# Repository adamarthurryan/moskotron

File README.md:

moskotron
=========

A unique analog audio synthesizer. Built with and for Alex Moskos - aka Drainolith. 

Audio is generated by a Korg Monotron, which is extended by wiring in two new boards: 
an ADSR enveloped waveshaper and a 5-key tunable touch keyboard.
The keyboard can be tuned to any scale - conventional, microtonal or weird.

The entire synthesizer was encased in a book - for effect.

See http://madanworb.com/blog/2012/08/15/moskotron/ for video of Alex trying it out for the first time.

Schematics and burnable pcb layouts are available in the documentation folder.

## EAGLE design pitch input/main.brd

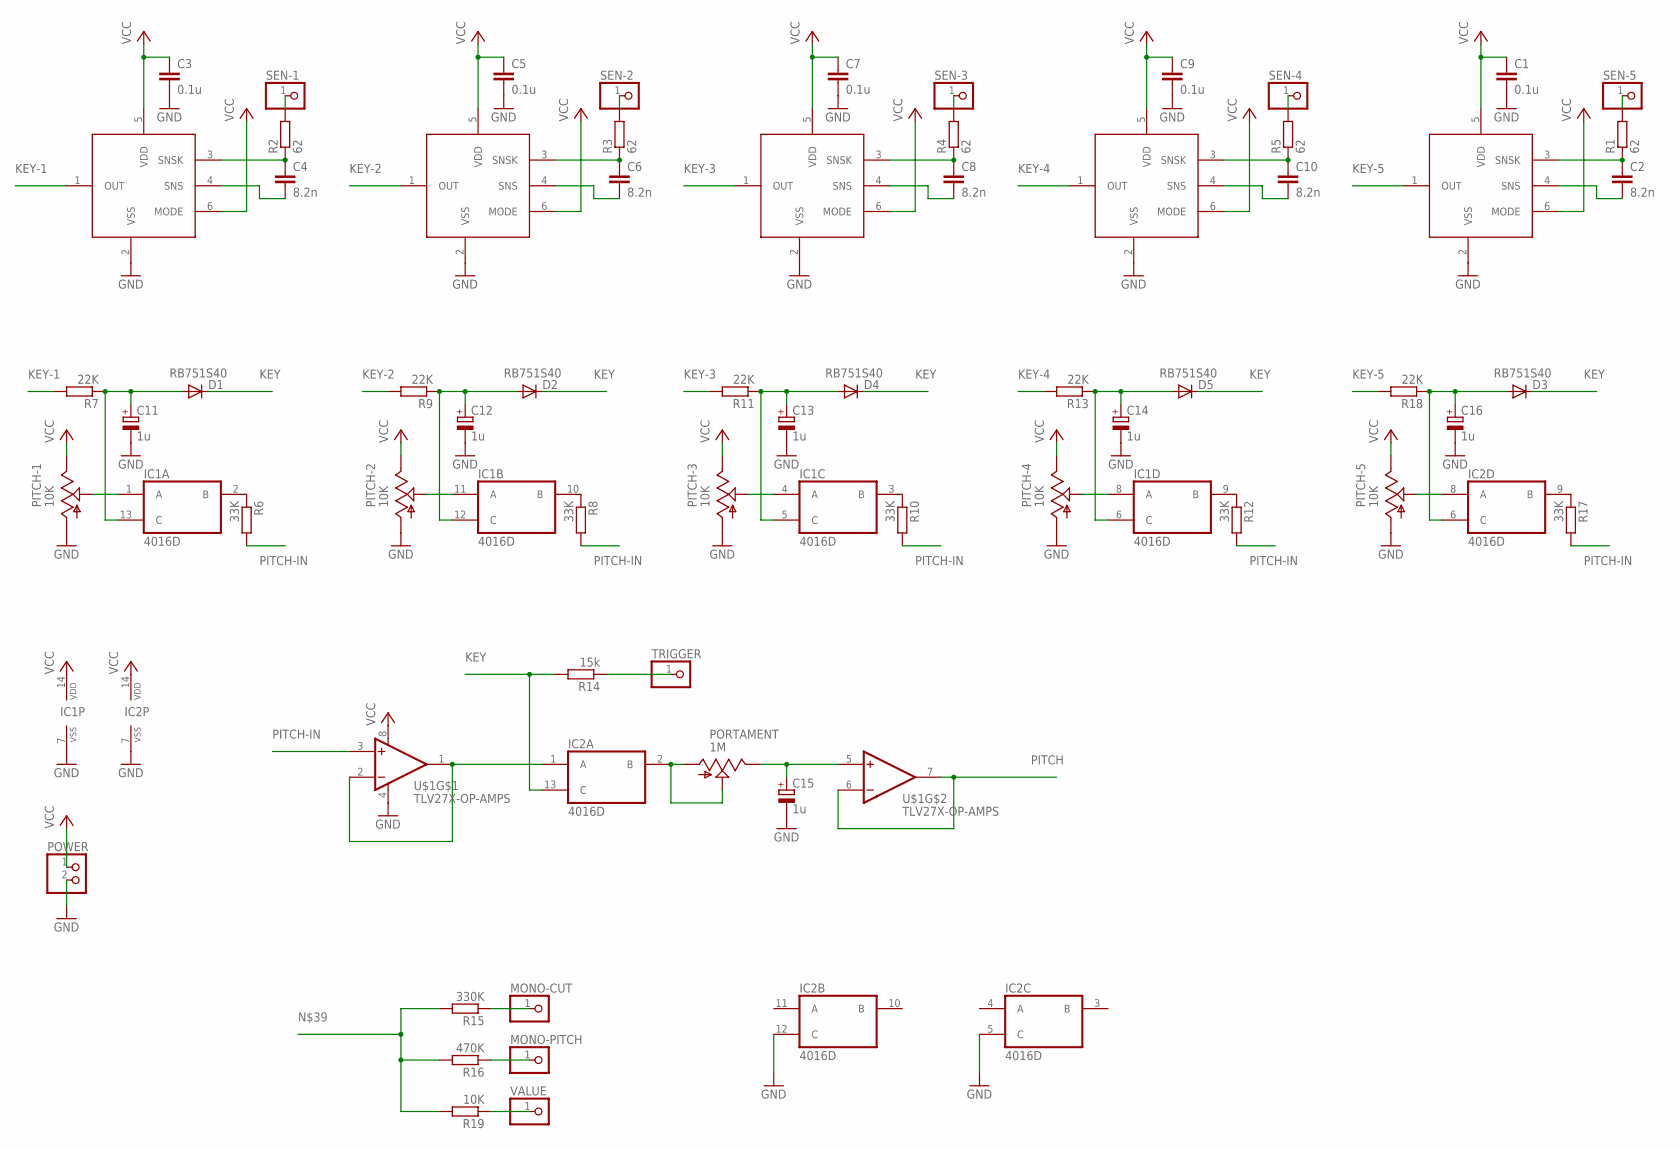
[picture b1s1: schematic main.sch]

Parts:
C1, C3, C5, C7, C9: 0.1u; C0805
C2, C4, C6, C8, C10: 8.2n; C0805
C11, C12, C13, C14, C15, C16: 1u; PANASONIC_A
D1, D2, D3, D4, D5: RB751S40; SOD523
IC1, IC2: 4016D; SO14
MONO-CUT: PINHD-1X1; 1X01
MONO-PITCH: PINHD-1X1; 1X01
PITCH-1, PITCH-2, PITCH-3, PITCH-4, PITCH-5: 10K; PIN-1X03
PORTAMENT: 1M; PIN-1X03
POWER: PINHD-1X2; 1X02
R1, R2, R3, R4, R5: 62; R0805
R6, R8, R10, R12, R17: 33K; R0805
R7, R9, R11, R13, R18: 22K; R0805
R14: 15k; R0805
R15: 330K; R0805
R16: 470K; R0805
R19: 10K; R0805
SEN-1, SEN-2, SEN-3, SEN-4, SEN-5: PINHD-1X1; 1X01
TRIGGER: PINHD-1X1; 1X01
U$1: TLV27X-OP-AMPS; SOIC8
U$2, U$3, U$4, U$5, U$6: AT42QT1010; SOT23-6L
VALUE: PINHD-1X1; 1X01

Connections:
GND: C1.2, C3.2, C5.2, C7.2, C9.2, C11.-, C12.-, C13.-, C14.-, C15.-, C16.-, IC1.7 (VSS), IC2.5 (C), IC2.7 (VSS), IC2.12 (C), PITCH-1.1 (A), PITCH-2.1 (A), PITCH-3.1 (A), PITCH-4.1 (A), PITCH-5.1 (A), POWER.2, U$1.4 (V-), U$2.2 (VSS), U$3.2 (VSS), U$4.2 (VSS), U$5.2 (VSS), U$6.2 (VSS)
KEY: D1.C, D2.C, D3.C, D4.C, D5.C, IC2.13 (C), R14.2
KEY-1: R7.2, U$2.1 (OUT)
KEY-2: R9.2, U$3.1 (OUT)
KEY-3: R11.2, U$4.1 (OUT)
KEY-4: R13.2, U$5.1 (OUT)
KEY-5: R18.2, U$6.1 (OUT)
unnamed: C4.2, U$2.4 (SNS)
unnamed: C4.1, R2.1, U$2.3 (SNSK)
unnamed: R2.2, SEN-1.1
unnamed: C6.2, U$3.4 (SNS)
unnamed: C6.1, R3.1, U$3.3 (SNSK)
unnamed: R3.2, SEN-2.1
unnamed: C8.2, U$4.4 (SNS)
unnamed: C8.1, R4.1, U$4.3 (SNSK)
unnamed: R4.2, SEN-3.1
unnamed: C10.2, U$5.4 (SNS)
unnamed: C10.1, R5.1, U$5.3 (SNSK)
unnamed: R5.2, SEN-4.1
unnamed: IC1.1 (A), PITCH-1.2 (S)
unnamed: IC1.2 (B), R6.1
unnamed: C11.+, D1.A, IC1.13 (C), R7.1
unnamed: IC1.11 (A), PITCH-2.2 (S)
unnamed: IC1.10 (B), R8.1
unnamed: C12.+, D2.A, IC1.12 (C), R9.1
unnamed: IC1.4 (A), PITCH-3.2 (S)
unnamed: IC1.3 (B), R10.1
unnamed: C13.+, D4.A, IC1.5 (C), R11.1
unnamed: IC1.8 (A), PITCH-4.2 (S)
unnamed: IC1.9 (B), R12.1
unnamed: C14.+, D5.A, IC1.6 (C), R13.1
unnamed: IC2.1 (A), U$1.1 (OUT), U$1.2 (-IN)
unnamed: IC2.2 (B), PORTAMENT.1 (A), PORTAMENT.2 (S)
unnamed: MONO-PITCH.1, R16.1
unnamed: C15.+, PORTAMENT.3 (E), U$1.5 (+IN)
unnamed: MONO-CUT.1, R15.1
unnamed: C2.2, U$6.4 (SNS)
unnamed: C2.1, R1.1, U$6.3 (SNSK)
unnamed: R1.2, SEN-5.1
unnamed: IC2.8 (A), PITCH-5.2 (S)
unnamed: C16.+, D3.A, IC2.6 (C), R18.1
unnamed: IC2.9 (B), R17.1
unnamed: R15.2, R16.2, R19.2
unnamed: R19.1, VALUE.1
PITCH: U$1.6 (-IN), U$1.7 (OUT)
PITCH-IN: R6.2, R8.2, R10.2, R12.2, R17.2, U$1.3 (+IN)
TRIG: R14.1, TRIGGER.1
VCC: C1.1, C3.1, C5.1, C7.1, C9.1, IC1.14 (VDD), IC2.14 (VDD), PITCH-1.3 (E), PITCH-2.3 (E), PITCH-3.3 (E), PITCH-4.3 (E), PITCH-5.3 (E), POWER.1, U$1.8 (V+), U$2.5 (VDD), U$2.6 (MODE), U$3.5 (VDD), U$3.6 (MODE), U$4.5 (VDD), U$4.6 (MODE), U$5.5 (VDD), U$5.6 (MODE), U$6.5 (VDD), U$6.6 (MODE)

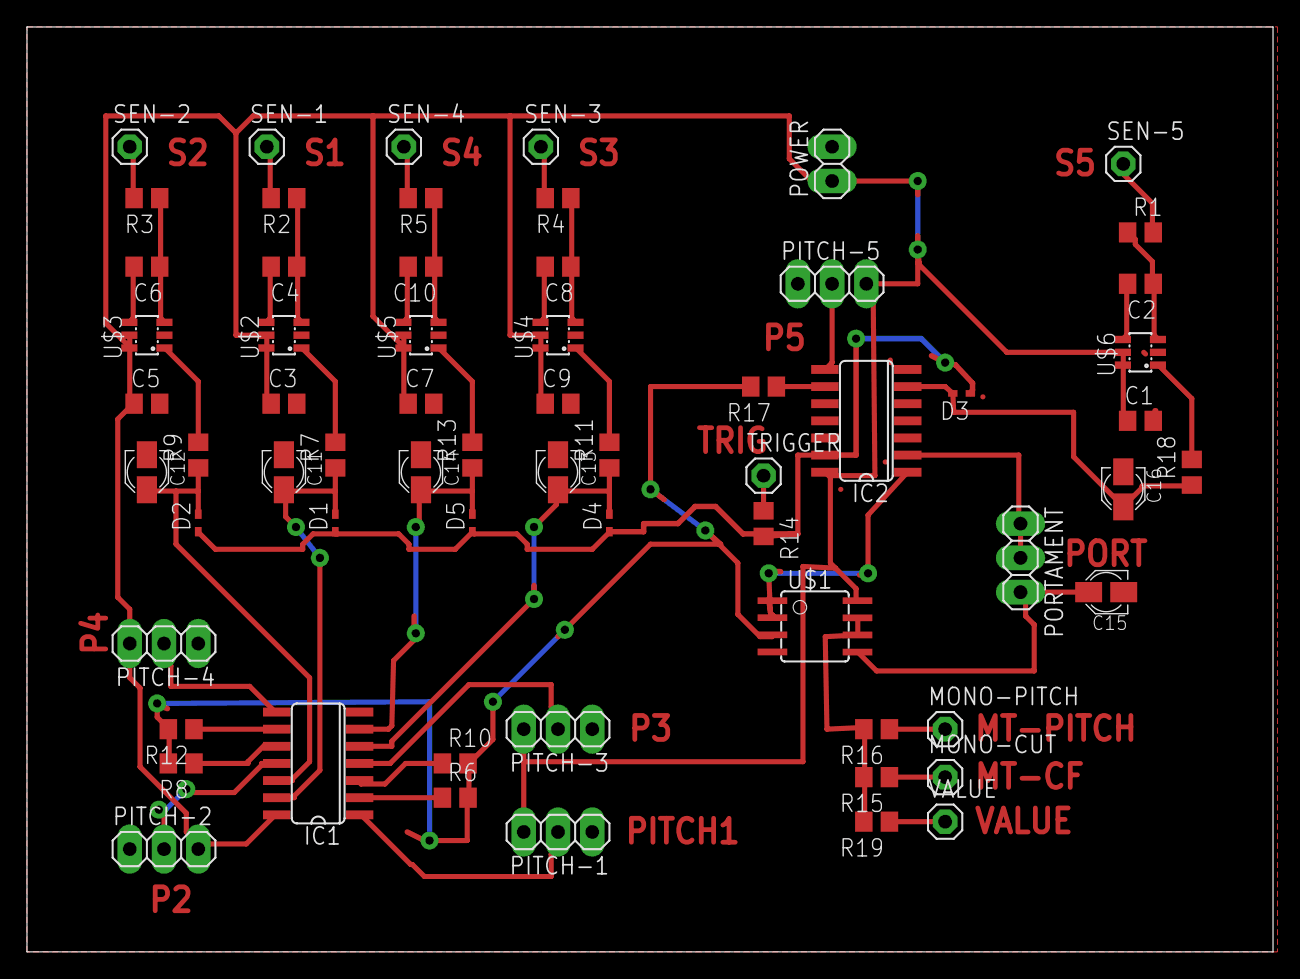
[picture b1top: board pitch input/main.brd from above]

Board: 2 copper layers, 92.4 x 68.6 mm, 64 parts (0 on the bottom side), 48 nets.

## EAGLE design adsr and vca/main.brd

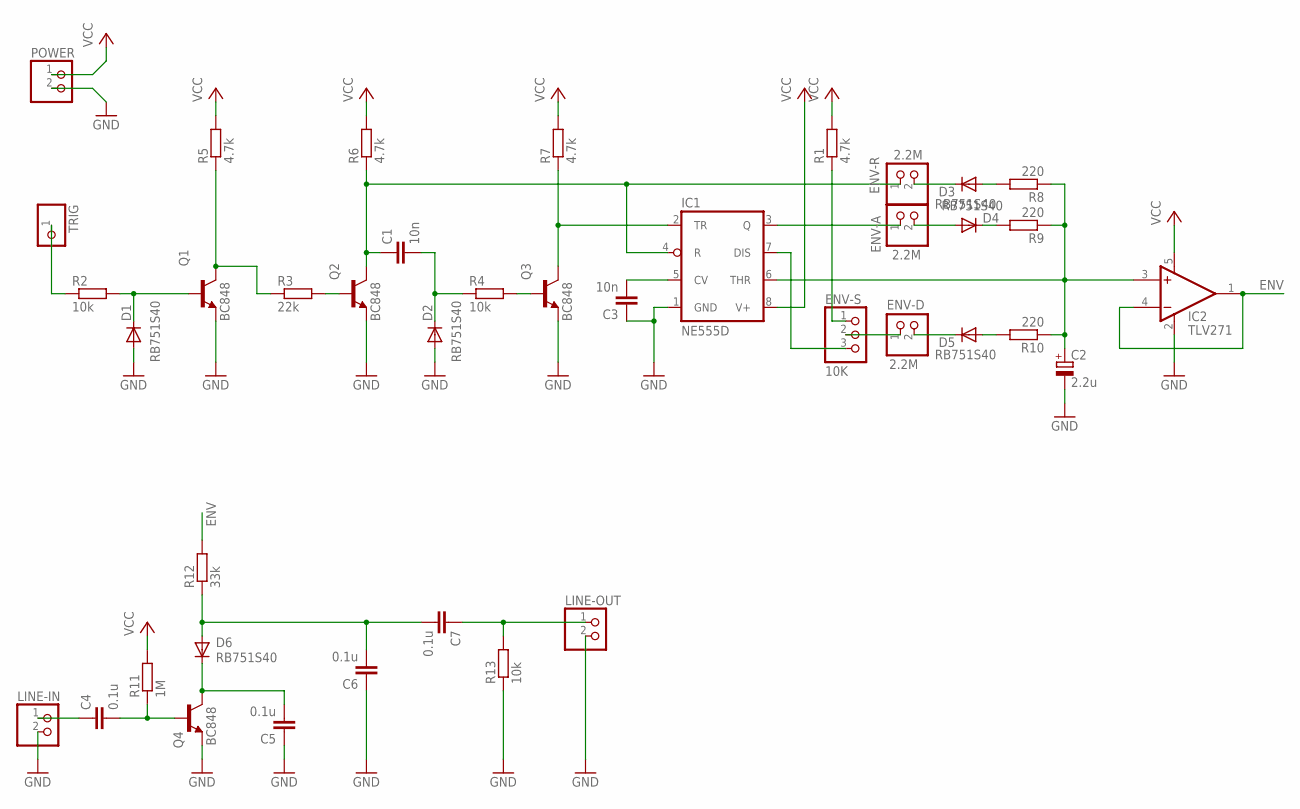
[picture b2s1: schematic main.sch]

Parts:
C1, C3: 10n; C0805
C2: 2.2u; PANASONIC_A
C4, C5, C6, C7: 0.1u; C0805
D1, D2, D3, D4, D5, D6: RB751S40; SOD523
ENV-A: 2.2M; 1X02M
ENV-D: 2.2M; 1X02M
ENV-R: 2.2M; 1X02M
ENV-S: 10K; 1X03M
IC1: NE555D; SO08
IC2: TLV271; SOT23-5
LINE-IN: PINHD-1X02_2.00; 1X02M
LINE-OUT: PINHD-1X02_2.00; 1X02M
POWER: PINHD-1X02_2.00; 1X02M
Q1, Q2, Q3, Q4: BC848; SOT23
R1, R5, R6, R7: 4.7k; R0805W
R2, R4, R13: 10k; R0805W
R3: 22k; R0805W
R8, R9, R10: 220; R0805W
R11: 1M; R0805W
R12: 33k; R0805W
TRIG: PINHD-1X01_2.00; 1X01M

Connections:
ENV: IC2.1 (OUT), IC2.4 (-IN), R12.2
GND: C2.-, C3.1, C5.1, C6.1, D1.A, D2.A, IC1.1 (GND), IC2.2 (V-), LINE-IN.2, LINE-OUT.2, POWER.2, Q1.2 (E), Q2.2 (E), Q3.2 (E), Q4.2 (E), R13.1
unnamed: R2.1, TRIG.1
unnamed: D1.C, Q1.1 (B), R2.2
unnamed: Q1.3 (C), R3.1, R5.1
unnamed: Q2.1 (B), R3.2
unnamed: C1.1, ENV-R.1, IC1.4 (R), Q2.3 (C), R6.1
unnamed: C1.2, D2.C, R4.1
unnamed: Q3.1 (B), R4.2
unnamed: C7.1, LINE-OUT.1, R13.2
unnamed: D5.C, ENV-D.2
unnamed: ENV-D.1, ENV-S.2
unnamed: ENV-S.3, IC1.7 (DIS)
unnamed: IC1.2 (TR), Q3.3 (C), R7.1
unnamed: C3.2, IC1.5 (CV)
unnamed: D3.A, R8.2
unnamed: D3.C, ENV-R.2
unnamed: C2.+, IC1.6 (THR), IC2.3 (+IN), R8.1, R9.1, R10.1
unnamed: ENV-A.1, IC1.3 (Q)
unnamed: D4.A, ENV-A.2
unnamed: D4.C, R9.2
unnamed: D5.A, R10.2
unnamed: ENV-S.1, R1.1
unnamed: C4.1, LINE-IN.1
unnamed: C4.2, Q4.1 (B), R11.1
unnamed: C5.2, D6.C, Q4.3 (C)
unnamed: C6.2, C7.2, D6.A, R12.1
VCC: IC1.8 (V+), IC2.5 (V+), POWER.1, R1.2, R5.2, R6.2, R7.2, R11.2

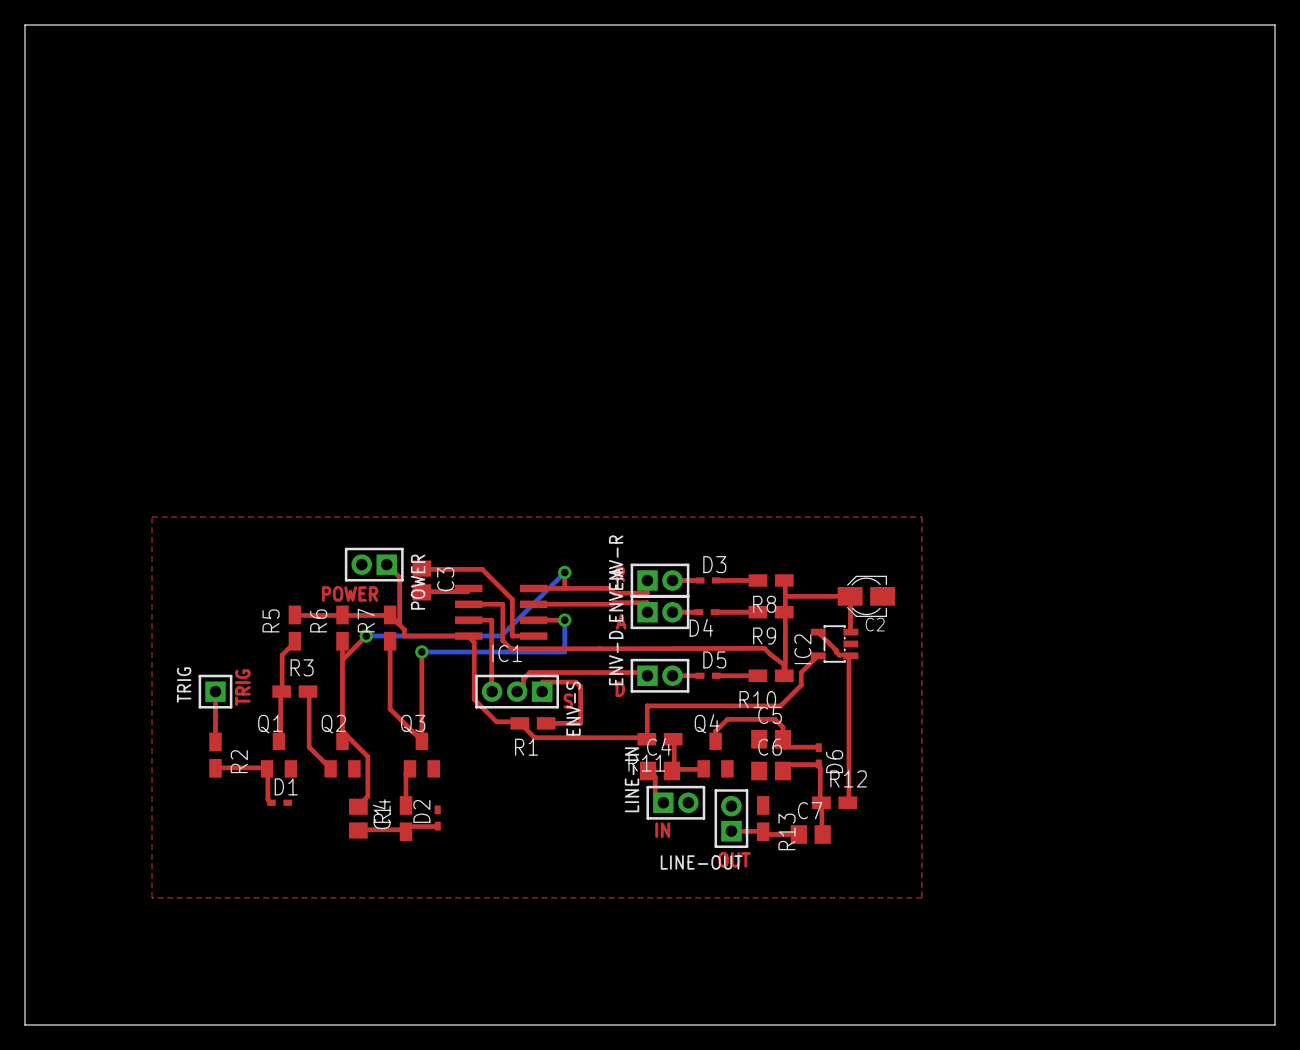
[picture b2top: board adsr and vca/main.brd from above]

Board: 2 copper layers, 100.0 x 80.0 mm, 40 parts (0 on the bottom side), 28 nets.

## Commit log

2014-11-22 added project description
2014-11-22 initial project files check in
